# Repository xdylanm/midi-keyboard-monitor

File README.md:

# MKM — Core Music Trainer

A cross-platform piano practice application with MIDI transcription, sheet music display and light editing, performance accuracy analytics, and a dual agent interface (REST + MCP-compatible tools).

## Platform targets

- **Ubuntu desktop** and **Windows 11 desktop/laptop** — browser-first, later packaged with Tauri.
- **Android** — optional web-browser client in a future release; no native app in v1.

## Architecture summary

- **Core**: Python 3.11 service layer (FastAPI, music21, mido, librosa, python-rtmidi).
- **UI**: React frontend served locally; score rendering via OpenSheetMusicDisplay (VexFlow/MusicXML).
- **Packaging**: browser-first → Tauri desktop shell once workflows stabilize.
- **Agent interfaces**: REST API (OpenAPI) and MCP-compatible tool adapter over the same internal service contract.
- **MIDI input**: abstract `MidiSource` interface supports the project's BLE dongle and any USB class-compliant MIDI device.
- **Future**: Rust core replacement via stable API contract; UI and agent interfaces unchanged.

## Hardware and firmware

The hardware (KiCad PCB) and firmware (MicroPython BLE MIDI dongle) are unchanged and out of scope for this development track. See [docs/assembly.md](docs/assembly.md) and [docs/firmware-spec.md](docs/firmware-spec.md).

## Documentation

- **[docs/development-plan.md](docs/development-plan.md)** — Product Requirements Document (authoritative).
- [docs/dynamics-tracking.md](docs/dynamics-tracking.md) — Legacy dynamics-tracking spec (historical reference only).
- [docs/design.md](docs/design.md) — Hardware design notes.
- [docs/firmware-spec.md](docs/firmware-spec.md) — BLE MIDI firmware specification.

## Windows development setup

python-rtmidi must be compiled from source on Windows. The build requires:

1. **LLVM/Clang** — install from [llvm.org](https://llvm.org/); ensure `clang-cl` is on your `PATH`.
2. **MSVC build tools** — install via the Visual Studio installer; select:
   - *MSVC v143 – VS 2022 C++ x64/x86 build tools (Latest)*
   - *Windows 11 SDK (latest)*
3. Add `.vscode/settings.json` and set `CC=clang-cl` and `CXX=clang-cl` for all integrated terminals, so `pip install -r requirements.txt` will work without further configuration inside VS Code.

```json
{
  "terminal.integrated.env.windows": {
    "CC": "clang-cl",
    "CXX": "clang-cl"
  }
}
```

Outside VS Code (e.g. CI), set those variables manually before running pip:

```powershell
$env:CC = "clang-cl"; $env:CXX = "clang-cl"
pip install -r requirements.txt
```

## Flutter prototype (legacy)

The `app/` directory contains a Flutter/Android prototype from the earlier dynamics-tracking phase. It is retained as a reference for BLE-MIDI packet parsing and dynamics scoring logic but is not the active development path. See [app/README.md](app/README.md).

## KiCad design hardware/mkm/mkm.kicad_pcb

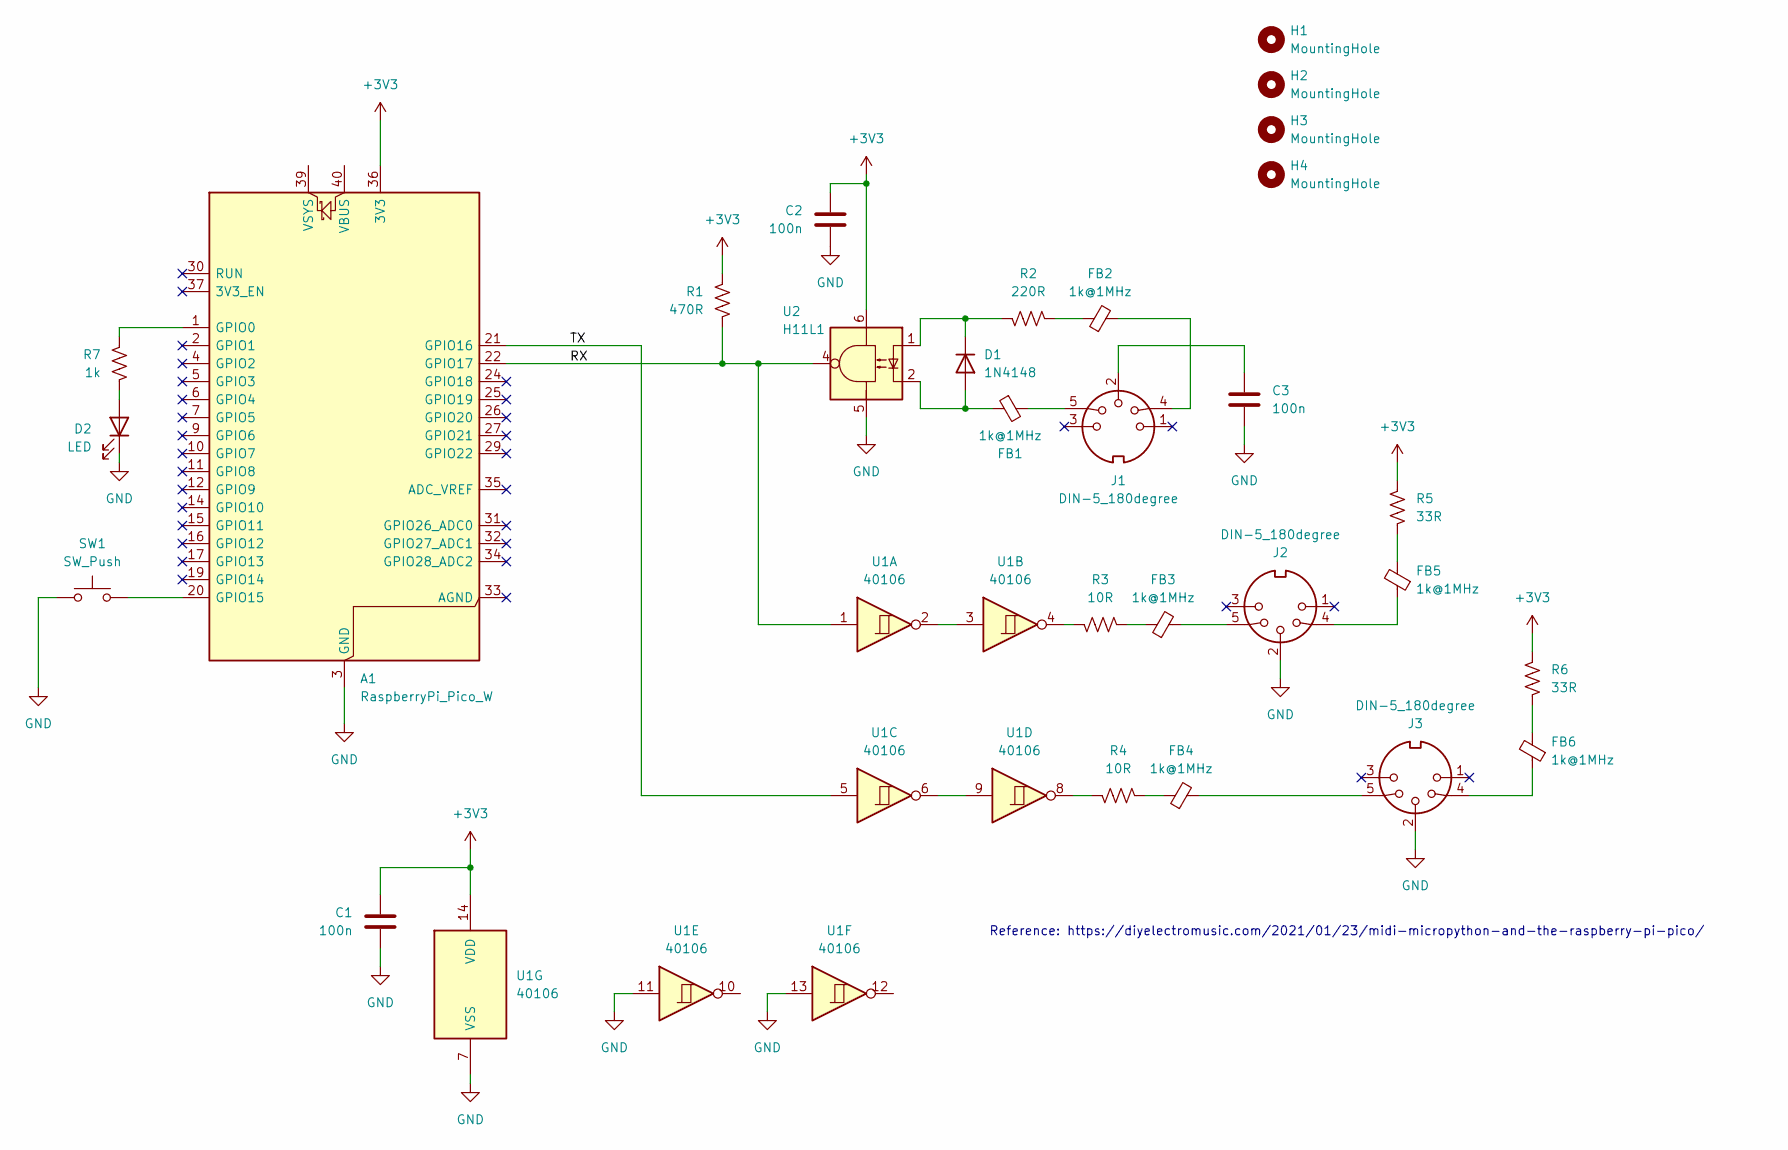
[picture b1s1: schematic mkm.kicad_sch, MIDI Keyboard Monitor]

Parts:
A1: RaspberryPi_Pico_W; RaspberryPi_Pico_Common_THT
C1, C2, C3: 100n; C_Disc_D5.1mm_W3.2mm_P5.00mm
D1: 1N4148; D_DO-35_SOD27_P7.62mm_Horizontal
D2: LED; LED_D5.0mm_Clear
FB1, FB2, FB3, FB4, FB5, FB6: 1k@1MHz; L_Axial_L7.0mm_D3.3mm_P2.54mm_Vertical_Fastron_MICC
H1, H2, H3, H4: MountingHole; MountingHole_3.2mm_M3_DIN965
J1, J2, J3: DIN-5_180degree; CUI_SDS-50J
R1: 470R; R_Axial_DIN0207_L6.3mm_D2.5mm_P7.62mm_Horizontal
R2: 220R; R_Axial_DIN0207_L6.3mm_D2.5mm_P7.62mm_Horizontal
R3, R4: 10R; R_Axial_DIN0207_L6.3mm_D2.5mm_P7.62mm_Horizontal
R5, R6: 33R; R_Axial_DIN0207_L6.3mm_D2.5mm_P7.62mm_Horizontal
R7: 1k; R_Axial_DIN0207_L6.3mm_D2.5mm_P7.62mm_Horizontal
SW1: SW_Push; SW_PUSH_6mm
U1: 40106; DIP-14_W7.62mm_Socket
U2: H11L1; DIP-6_W7.62mm_Socket

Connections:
+3V3: A1.36 (3V3), C1.1, C2.1, R1.2, R5.1, R6.1, U1.14 (VDD), U2.6
/RX: A1.22 (GPIO17), R1.1, U1.1, U2.4
/TX: A1.21 (GPIO16), U1.5
GND: A1.3 (GND), A1.8 (GND), A1.13 (GND), A1.18 (GND), A1.23 (GND), A1.28 (GND), A1.38 (GND), C1.2, C2.2, C3.2, D2.1 (K), J2.2, J3.2, SW1.1, U1.7 (VSS), U1.11, U1.13, U2.5
unnamed: A1.1 (GPIO0), R7.2
unnamed: A1.20 (GPIO15), SW1.2
unnamed: C3.1, J1.2
unnamed: D1.2 (A), FB1.1, U2.2
unnamed: D1.1 (K), R2.2, U2.1
unnamed: D2.2 (A), R7.1
unnamed: FB1.2, J1.5
unnamed: FB2.1, R2.1
unnamed: FB2.2, J1.4
unnamed: FB3.1, R3.1
unnamed: FB3.2, J2.5
unnamed: FB4.1, R4.1
unnamed: FB4.2, J3.5
unnamed: FB5.1, J2.4
unnamed: FB5.2, R5.2
unnamed: FB6.1, J3.4
unnamed: FB6.2, R6.2
unnamed: R3.2, U1.4
unnamed: R4.2, U1.8
unnamed: U1.2, U1.3
unnamed: U1.6, U1.9

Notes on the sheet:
Reference: https://diyelectromusic.com/2021/01/23/midi-micropython-and-the-raspberry-pi-pico/

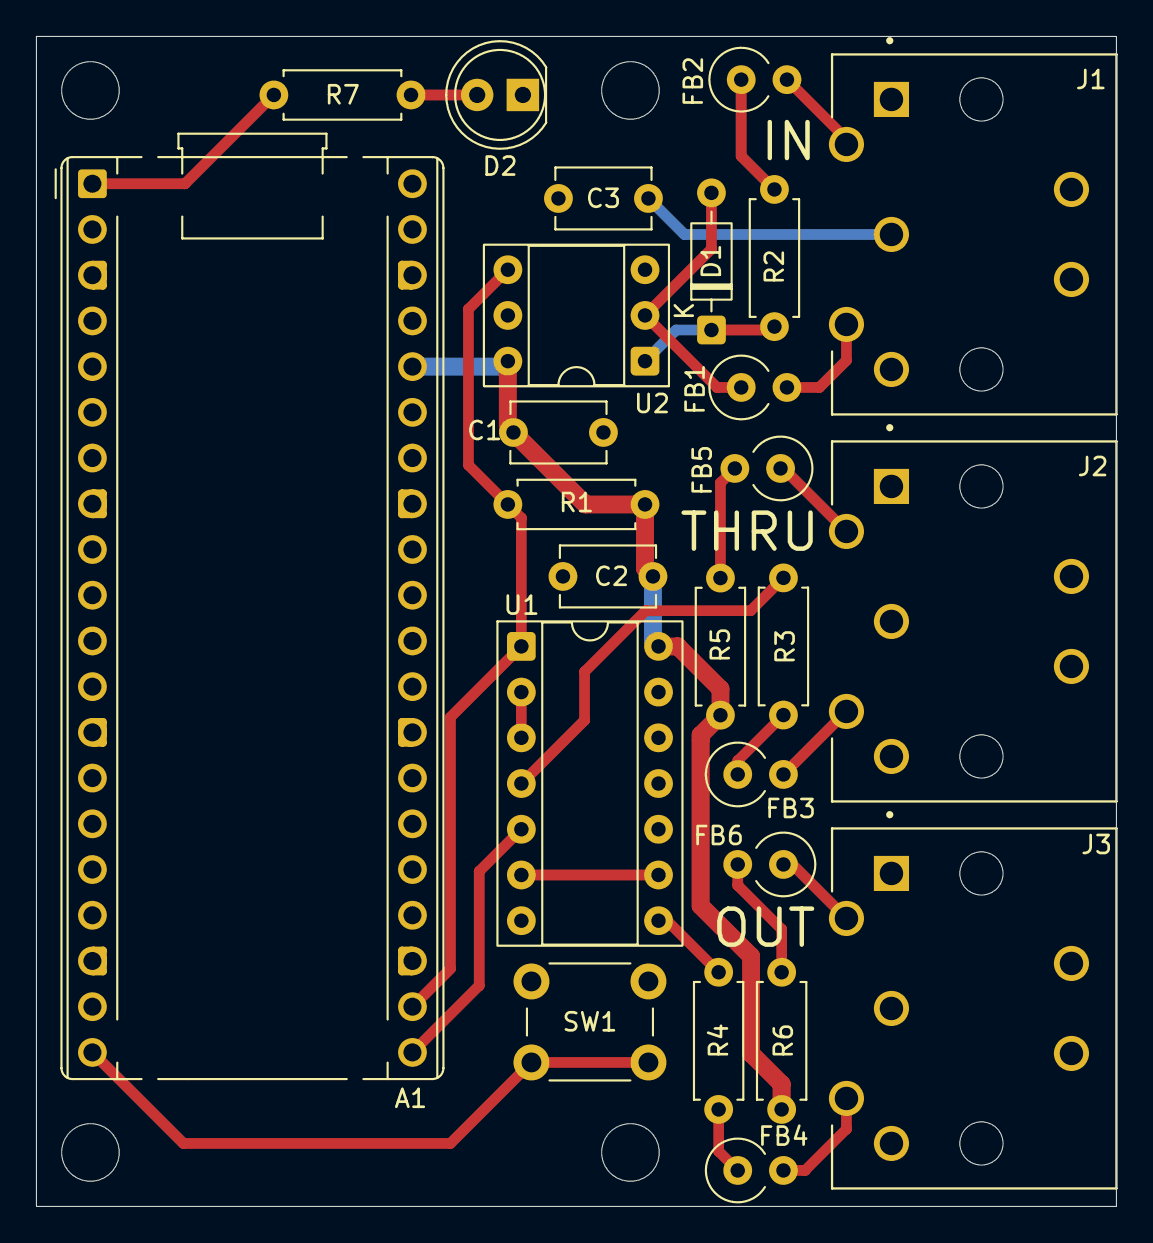
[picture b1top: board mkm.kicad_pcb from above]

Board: 2 copper layers, 60.0 x 65.0 mm, 29 parts (0 on the bottom side), 25 nets.

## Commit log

2025-12-20 Sketched schematic, initial pass at the firmware using GHCP agent with GPT-5 mini to do most of the heavy lifting.
2025-12-24 minor tweaks
2025-12-24 Converting to an Android app with BLE MIDI. Initial PoC for the app with mocked out data
2025-12-25 Sending simulated MIDI packets via BLE to the app (all in debug mode)
2025-12-26 Tested and confirmed with a physically connected keyboard via MIDI
2025-12-26 Cleaned up firmware and fixed issue with UART pin conflict when using pin 0 for the LED (override UART default for TX pin)
2025-12-26 Adding scanning/re-scanning on disconnects and some handling for scenarios when BT is turned off when the app launches
2025-12-26 Developed spec for the app
2025-12-27 added detailed development plan and WIP on milestone 1
2026-01-02 WIP on practice plan config page
2026-01-09 Practice plan settings page looks OK
2026-05-27 Refactor practice plan schema: remove octaveIndex and update intensity fields to use strings
2026-05-29 Removed old Flutter app; Defined PRD and design/tasks for M1
2026-05-29 Add M1 manual score generation and validation tests
    - Introduced a script to generate a C-major scale exercise in MusicXML and MIDI formats for manual validation.
    - Added pytest configuration to streamline test discovery.
    - Updated requirements to include necessary libraries for music processing and testing.
    - Created a suite of tests for MIDI I/O, MusicXML round-trip validation, and sidecar schema validation.
    - Implemented fixtures for valid and invalid sidecar JSON files to ensure schema compliance.
    - Added helper functions for fixture path resolution and event summary assertions.
2026-05-29 Add BLE and USB MIDI input tests with mock adapters
    - Implemented `ble_input_test.py` for testing BLE MIDI input from a dongle.
    - Implemented `usb_input_test.py` for testing USB MIDI input from a keyboard.
    - Created shared mock helpers in `helpers.py` to simulate MIDI input without hardware.
    - Added unit tests for `BleAdapter` in `test_ble_adapter.py`, covering packet parsing and lifecycle management.
    - Added contract tests for `MidiSource` interface in `test_midi_source_contract.py` to ensure both `UsbMidiAdapter` and `BleAdapter` conform to the same API.
    - Added unit tests for `UsbMidiAdapter` in `test_usb_adapter.py`, focusing on message parsing and lifecycle management.
2026-05-29 Add Windows development setup instructions for python-rtmidi compilation
2026-05-29 Enhance BLE adapter functionality and add connection smoke test
    - Introduced caching for BLE devices in BleAdapter to avoid redundant scans.
    - Updated device scanning logic to utilize cached devices for connections.
    - Improved BLE-MIDI packet encoding to align with the BLE-MIDI 1.0 specification.
    - Added a new diagnostic script for testing BLE connections without a MIDI keyboard.
    - Refactored existing BLE input test to utilize the updated BleAdapter methods.
2026-05-29 Fixing timestamp header for BT packets

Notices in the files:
hardware/mkm/mkm.kicad_pcb:
CC BY-SA 4.0
